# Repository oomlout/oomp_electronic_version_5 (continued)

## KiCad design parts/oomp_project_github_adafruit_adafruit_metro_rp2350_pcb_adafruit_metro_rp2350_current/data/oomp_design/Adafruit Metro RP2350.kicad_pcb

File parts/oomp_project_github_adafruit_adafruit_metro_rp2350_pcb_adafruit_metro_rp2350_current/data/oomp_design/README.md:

# OOMP KiCad design copy

Open `Adafruit Metro RP2350.kicad_pro` (or the `.kicad_pcb` / `.kicad_sch`) in KiCad. Local OOMP libraries are under `libraries/`. Original inputs are preserved in [../original/](../original/).

Only verified unchanged installed KiCad defaults were renamed. Modified, custom, unmatched and unavailable items remain unchanged. Soldering variants are never swapped during conversion. Existing pad coordinates, nets and UUIDs are preserved.

See [conversion_report.yaml](conversion_report.yaml) for every conversion and skip. Copy this directory before editing; regeneration refuses to overwrite edited design files.

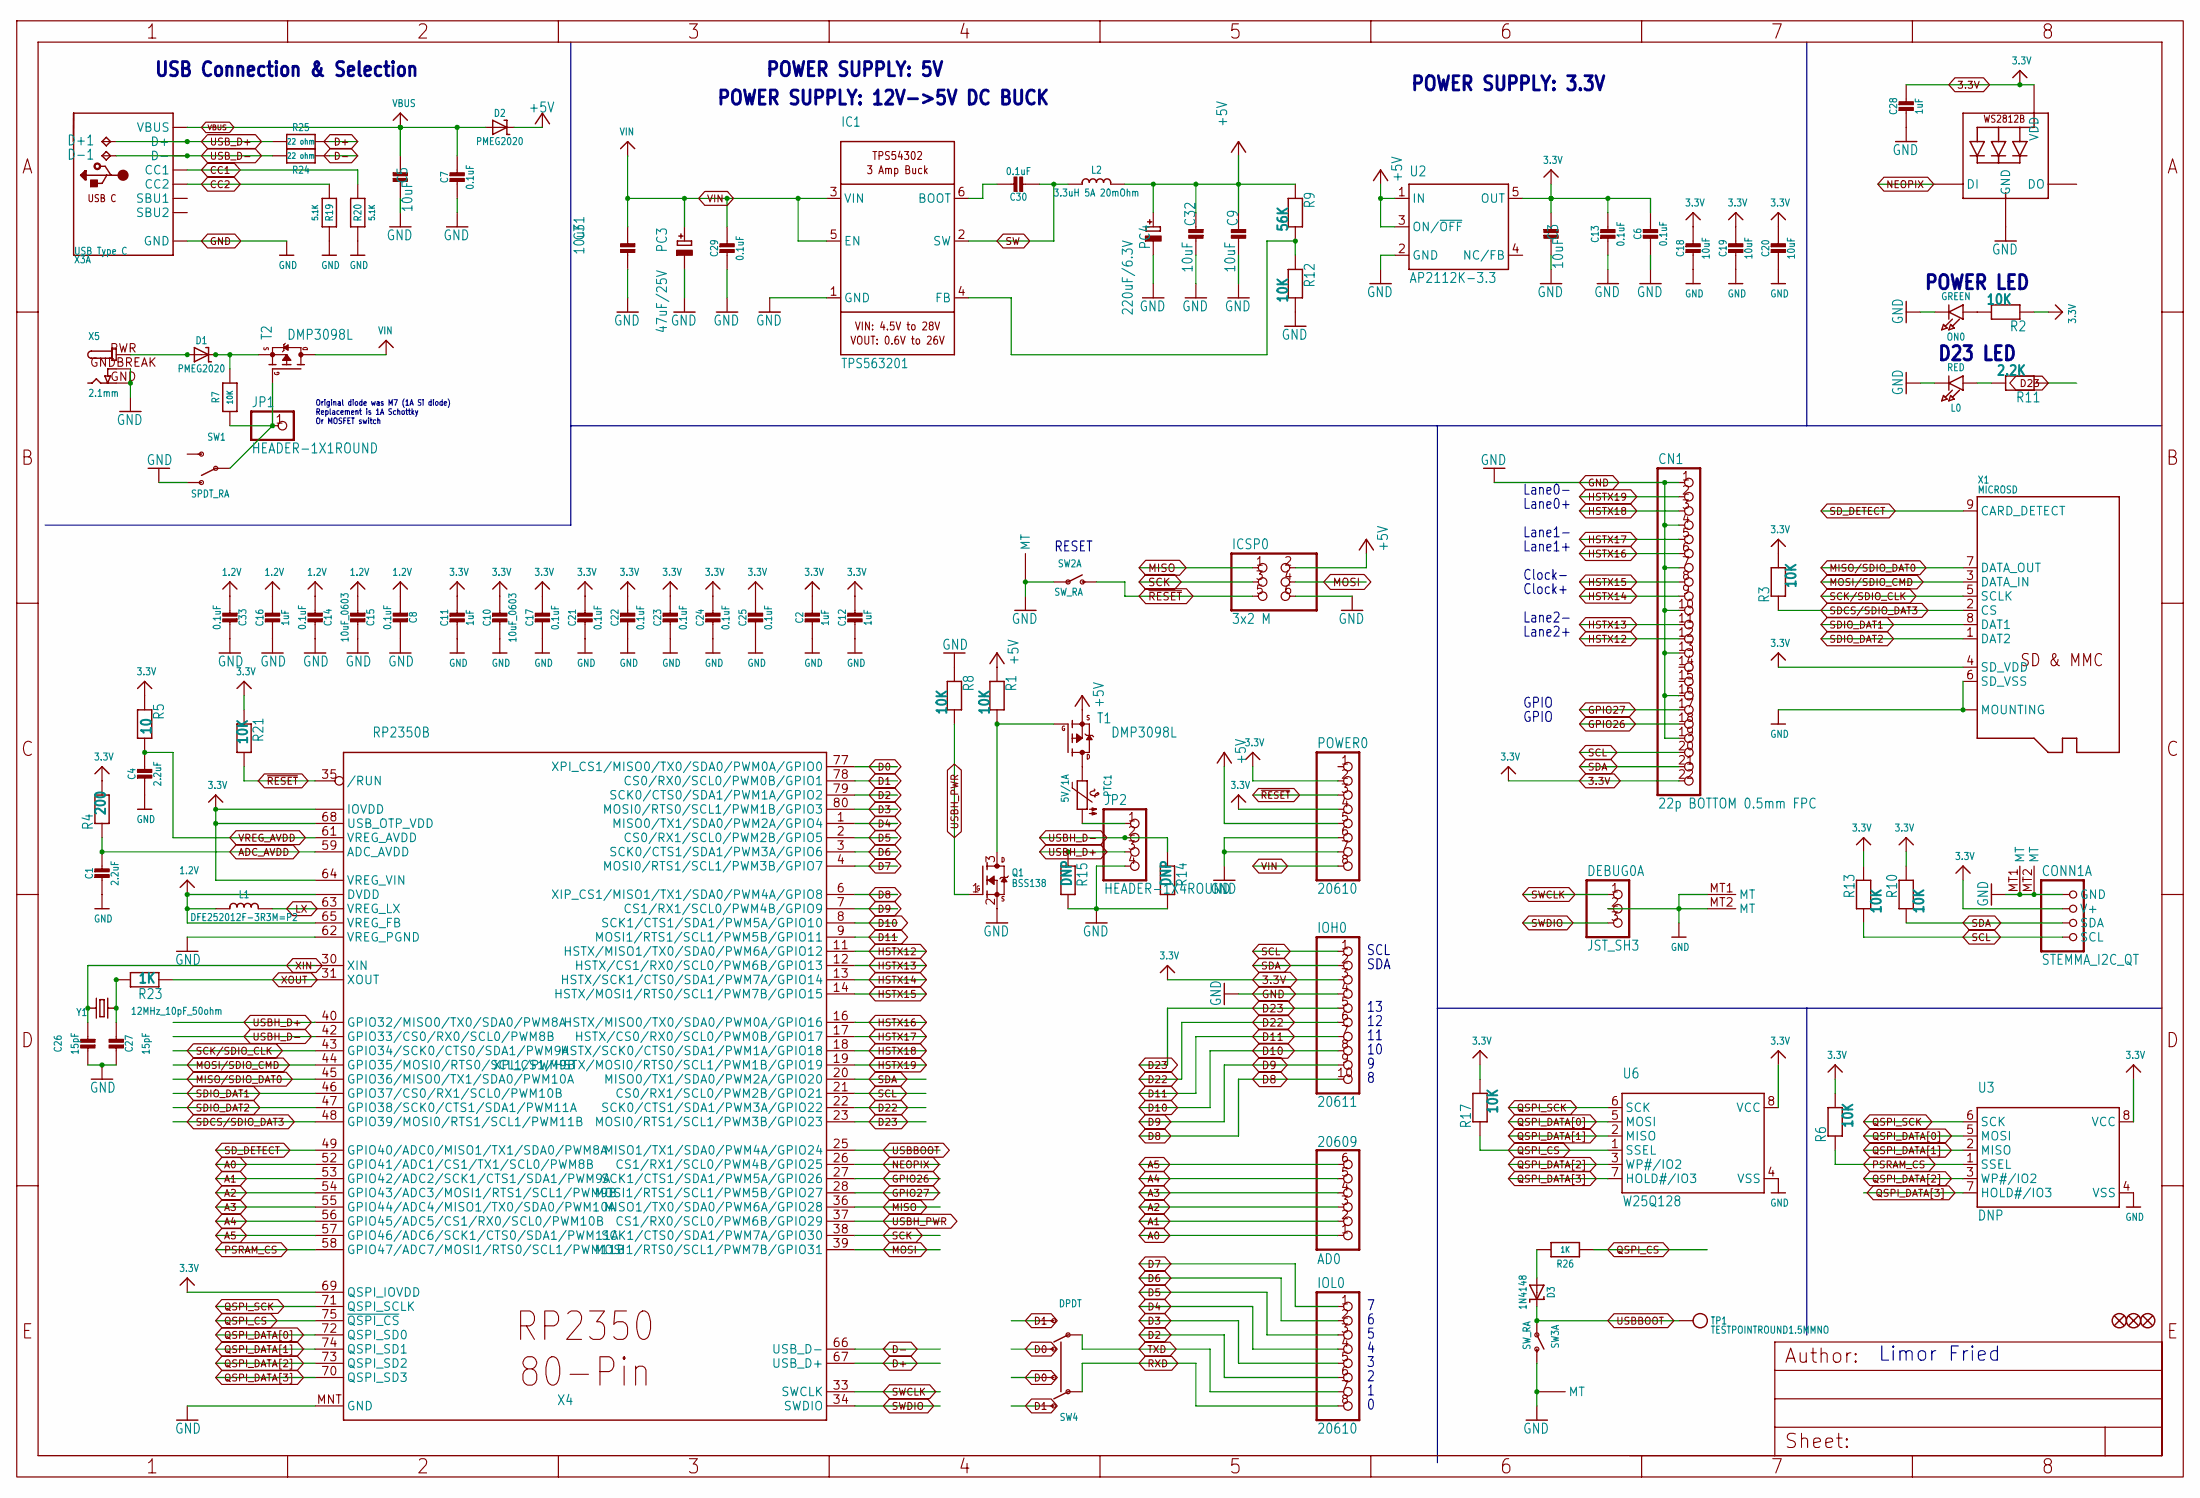
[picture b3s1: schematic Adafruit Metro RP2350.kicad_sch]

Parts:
AD0: 20609; 1X06_OVALWAVE
C1, C4: 2.2uF; 0603-NO
C2, C11, C12, C16, C28: 1uF; 0603-NO
C3, C5, C9, C18, C19, C20, C31, C32: 10uF; 0805-NO
C6, C7, C8, C13, C14, C17, C21, C22, C23, C24, C25, C29, C30, C33: 0.1uF; 0603-NO
C10, C15: 10uF_0603; 0603-NO_WIDE
C26, C27: 15pF; 0603-NO
CN1: 22p BOTTOM 0.5mm FPC; FPC_22PIN
CONN1: STEMMA_I2C_QT; JST_SH4; LCSC C2845363
D1, D2: PMEG2020; SOD-323
D3: 1N4148; SOD-323
D+1: TPB1,27; B1,27
D-1: TPB1,27; B1,27
DEBUG0: JST_SH3; JST_SH3_RA
FD1, FD2, FD3: FIDUCIAL_1MM
IC1: TPS563201; SOT23-6
ICSP0: 3x2 M; 2X03_ROUND_70MIL
IOH0: 20611; 1X10_OVALWAVE
IOL0: 20610; 1X08_OVALWAVE
JP1: HEADER-1X1ROUND; 1X01_ROUND
JP2: HEADER-1X4ROUND; 1X04_ROUND
L0: RED; CHIPLED_0603_NOOUTLINE
L1: DFE252012F-3R3M=P2; INDUCTOR_1007
L2: 3.3uH 5A 20mOhm; INDUCTOR_0603S
LED2: WS2812B_3535FULL; LED3535_FULLPADS
ON0: GREEN; CHIPLED_0603_NOOUTLINE
PC3: 47uF/25V; PANASONIC_D
PC4: 220uF/6.3V; PANASONIC_D
POWER0: 20610; 1X08_OVALWAVE
PTC1: 5V/1A; 0805-NO
Q1: BSS138; SOT23-WIDE
R1, R2, R3, R6, R7, R8, R10, R12, R13, R17, R21: 10K; 0603-NO
R4: 200; 0603-NO
R5: 10; 0603-NO
R9: 56K; 0603-NO
R11: 2.2K; 0603-NO
R14, R15: DNP; 0603-NO
R19, R20: 5.1K; 0603-NO
R23, R26: 1K; 0603-NO
R24, R25: 22 ohm; 0603-NO
SW1: SPDT_RA; SPDT_SMT_SSSS811101
SW2, SW3: SW_RA; SPST_TACTILE_RA; LCSC C778159
SW4: DPDT; EG1390; LCSC C2837066
T1, T2: DMP3098L; SOT23-WIDE
TP1: TESTPOINTROUND1.5MMNO; TESTPOINT_ROUND_1.5MM_NO
U2: AP2112K-3.3; SOT23-DBV
U3: DNP; SOIC8_208MIL
U6: W25Q128; SOIC8_208MIL
X1: MICROSD; MOLEX_104031-0811
X3: USB Type C; USB_C_CUSB31-CFM2AX-01-X; LCSC C165948
X4: RP2350B; QFN80
X5: 2.1mm; DCJACK_2MM_PTH
Y1: 12MHz_10pF_50ohm; CRYSTAL_2.5X2

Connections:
1.2V: C8.2, C14.2, C15.2, C16.1, C33.2, L1.P$1 (1), X4.10 (DVDD), X4.32 (DVDD), X4.51 (DVDD), X4.65 (VREG_FB)
3.3V: C2.1, C3.2, C6.2, C10.1, C11.1, C12.1, C13.1, C17.1, C18.1, C19.1, C20.1, C21.1, C22.1, C23.1, C24.1, C25.1, C28.1, CN1.22, CONN1.2 (V+), IOH0.3, LED2.2 (VDD), POWER0.2, POWER0.4, R2.1, R3.2, R4.2, R5.1, R6.2, R10.1, R13.1, R17.2, R21.1, U2.5 (OUT), U3.8 (VCC), U6.8 (VCC), X1.4 (SD_VDD), X4.5 (IOVDD), X4.15 (IOVDD), X4.24 (IOVDD), X4.29 (IOVDD), X4.41 (IOVDD), X4.50 (IOVDD), X4.60 (IOVDD), X4.64 (VREG_VIN), X4.68 (USB_OTP_VDD), X4.69 (QSPI_IOVDD), X4.76 (IOVDD)
+5V: C9.2, C32.2, D2.C, ICSP0.2, L2.P$2 (2), PC4.+, POWER0.5, R1.1, R9.1, T1.2 (S), U2.1 (IN), U2.3 (ON/~OFF)
A0: AD0.1, X4.52 (GPIO41/ADC1/CS1/TX1/SCL0/PWM8B)
A1: AD0.2, X4.53 (GPIO42/ADC2/SCK1/CTS1/SDA1/PWM9A)
A2: AD0.3, X4.54 (GPIO43/ADC3/MOSI1/RTS1/SCL1/PWM9B)
A3: AD0.4, X4.55 (GPIO44/ADC4/MISO1/TX0/SDA0/PWM10A)
A4: AD0.5, X4.56 (GPIO45/ADC5/CS1/RX0/SCL0/PWM10B)
A5: AD0.6, X4.57 (GPIO46/ADC6/SCK1/CTS0/SDA1/PWM11A)
ADC_AVDD: C1.1, R4.1, X4.59 (ADC_AVDD)
CC1: R20.2, X3.A5 (CC1)
CC2: R19.2, X3.B5 (CC2)
D0: SW4.O2, SW4.S1, X4.77 (XPI_CS1/MISO0/TX0/SDA0/PWM0A/GPIO0)
D1: SW4.O1, SW4.S2, X4.78 (CS0/RX0/SCL0/PWM0B/GPIO1)
D2: IOL0.6, X4.79 (SCK0/CTS0/SDA1/PWM1A/GPIO2)
D3: IOL0.5, X4.80 (MOSI0/RTS0/SCL1/PWM1B/GPIO3)
D4: IOL0.4, X4.1 (MISO0/TX1/SDA0/PWM2A/GPIO4)
D5: IOL0.3, X4.2 (CS0/RX1/SCL0/PWM2B/GPIO5)
D6: IOL0.2, X4.3 (SCK0/CTS1/SDA1/PWM3A/GPIO6)
D7: IOL0.1, X4.4 (MOSI0/RTS1/SCL1/PWM3B/GPIO7)
D8: IOH0.10, X4.6 (XIP_CS1/MISO1/TX1/SDA0/PWM4A/GPIO8)
D9: IOH0.9, X4.7 (CS1/RX1/SCL0/PWM4B/GPIO9)
D10: IOH0.8, X4.8 (SCK1/CTS1/SDA1/PWM5A/GPIO10)
D11: IOH0.7, X4.9 (MOSI1/RTS1/SCL1/PWM5B/GPIO11)
D22: IOH0.6, X4.22 (SCK0/CTS1/SDA1/PWM3A/GPIO22)
D23: IOH0.5, R11.1, X4.23 (MOSI0/RTS1/SCL1/PWM3B/GPIO23)
D+: R25.2, X4.67 (USB_D+)
D-: R24.2, X4.66 (USB_D-)
GND: C1.2, C2.2, C3.1, C4.2, C5.1, C6.1, C7.2, C8.1, C9.1, C10.2, C11.2, C12.2, C13.2, C14.1, C15.1, C16.2, C17.2, C18.2, C19.2, C20.2, C21.2, C22.2, C23.2, C24.2, C25.2, C26.1, C27.1, C28.2, C29.2, C31.1, C32.1, C33.1, CN1.1, CN1.4, CN1.7, CN1.10, CN1.13, CN1.16, CN1.19, CONN1.1 (GND), CONN1.MT1 (MT), CONN1.MT2 (MT), DEBUG0.2, DEBUG0.MT1 (MT), DEBUG0.MT2 (MT), IC1.1 (GND), ICSP0.6, IOH0.4, JP2.4, L0.C, LED2.4 (GND), ON0.C, PC3.-, PC4.-, POWER0.6, POWER0.7, Q1.2 (S), R8.1, R12.2, R14.1, R15.1, R19.1, R20.1, SW1.A (O), SW2.1, SW2.MT1 (MT), SW2.MT2 (MT), SW3.2 (S), SW3.MT1 (MT), SW3.MT2 (MT), U2.2 (GND), U3.4 (VSS), U6.4 (VSS), X1.6 (SD_VSS), X1.10 (MOUNTING), X1.G1 (MOUNTING), X1.G2 (MOUNTING), X1.G3 (MOUNTING), X1.G4 (MOUNTING), X3.A1B12 (GND), X3.B1A12 (GND), X4.62 (VREG_PGND), X4.MNT (GND), X5.GND, X5.GNDBREAK
GPIO26: CN1.18, X4.27 (SCK1/CTS1/SDA1/PWM5A/GPIO26)
GPIO27: CN1.17, X4.28 (MOSI1/RTS1/SCL1/PWM5B/GPIO27)
HSTX12: CN1.12, X4.11 (HSTX/MISO1/TX0/SDA0/PWM6A/GPIO12)
HSTX13: CN1.11, X4.12 (HSTX/CS1/RX0/SCL0/PWM6B/GPIO13)
HSTX14: CN1.9, X4.13 (HSTX/SCK1/CTS0/SDA1/PWM7A/GPIO14)
HSTX15: CN1.8, X4.14 (HSTX/MOSI1/RTS0/SCL1/PWM7B/GPIO15)
HSTX16: CN1.6, X4.16 (HSTX/MISO0/TX0/SDA0/PWM0A/GPIO16)
HSTX17: CN1.5, X4.17 (HSTX/CS0/RX0/SCL0/PWM0B/GPIO17)
HSTX18: CN1.3, X4.18 (HSTX/SCK0/CTS0/SDA1/PWM1A/GPIO18)
HSTX19: CN1.2, X4.19 (XPI_CS1/HSTX/MOSI0/RTS0/SCL1/PWM1B/GPIO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)
LX: L1.P$2 (2), X4.63 (VREG_LX)
MISO: ICSP0.1, X4.36 (MISO1/TX0/SDA0/PWM6A/GPIO28)
MISO/SDIO_DAT0: X1.7 (DATA_OUT), X4.45 (GPIO36/MISO0/TX1/SDA0/PWM10A)
MOSI: ICSP0.4, X4.39 (MOSI1/RTS0/SCL1/PWM7B/GPIO31)
MOSI/SDIO_CMD: X1.3 (DATA_IN), X4.44 (GPIO35/MOSI0/RTS0/SCL1/PWM9B)
unnamed: L0.A, R11.2
unnamed: ON0.A, R2.2
unnamed: JP2.1, PTC1.1
unnamed: PTC1.2, T1.3 (D)
unnamed: Q1.3 (D), R1.2, T1.1 (G)
unnamed: D3.A, R26.2
unnamed: C30.1, IC1.6 (BOOT)
unnamed: IC1.4 (FB), R9.2, R12.1
unnamed: C27.2, R23.1, Y1.3 (2)
unnamed: D1.C, R7.2, T2.2 (S)
NEOPIX: LED2.1 (DI), X4.26 (CS1/RX1/SCL0/PWM4B/GPIO25)
PSRAM_CS: R6.1, U3.1 (SSEL), X4.58 (GPIO47/ADC7/MOSI1/RTS0/SCL1/PWM11B)
PWRIN: D1.A, X5.PWR
PWR_SWITCH: JP1.1, R7.1, SW1.B, T2.1 (G)
QSPI_CS: R17.1, R26.1, U6.1 (SSEL), X4.75 (~QSPI_CS)
QSPI_DATA[0]: U3.5 (MOSI), U6.5 (MOSI), X4.72 (QSPI_SD0)
QSPI_DATA[1]: U3.2 (MISO), U6.2 (MISO), X4.74 (QSPI_SD1)
QSPI_DATA[2]: U3.3 (WP#/IO2), U6.3 (WP#/IO2), X4.73 (QSPI_SD2)
QSPI_DATA[3]: U3.7 (HOLD#/IO3), U6.7 (HOLD#/IO3), X4.70 (QSPI_SD3)
QSPI_SCK: U3.6 (SCK), U6.6 (SCK), X4.71 (QSPI_SCLK)
RXD: IOL0.8, SW4.P1
SCK: ICSP0.3, X4.38 (SCK1/CTS0/SDA1/PWM7A/GPIO30)
SCK/SDIO_CLK: X1.5 (SCLK), X4.43 (GPIO34/SCK0/CTS0/SDA1/PWM9A)
SCL: CN1.20, CONN1.4 (SCL), IOH0.1, R13.2, X4.21 (CS0/RX1/SCL0/PWM2B/GPIO21)
SDA: CN1.21, CONN1.3 (SDA), IOH0.2, R10.2, X4.20 (MISO0/TX1/SDA0/PWM2A/GPIO20)
SDCS/SDIO_DAT3: R3.1, X1.2 (CS), X4.48 (GPIO39/MOSI0/RTS1/SCL1/PWM11B)
SDIO_DAT1: X1.8 (DAT1), X4.46 (GPIO37/CS0/RX1/SCL0/PWM10B)
SDIO_DAT2: X1.1 (DAT2), X4.47 (GPIO38/SCK0/CTS1/SDA1/PWM11A)
SD_DETECT: X1.9 (CARD_DETECT), X4.49 (GPIO40/ADC0/MISO1/TX1/SDA0/PWM8A)
SW: C30.2, IC1.2 (SW), L2.P$1 (1)
SWCLK: DEBUG0.1, X4.33 (SWCLK)
SWDIO: DEBUG0.3, X4.34 (SWDIO)
TXD: IOL0.7, SW4.P2
USBBOOT: D3.C, SW3.1, TP1.P$1, X4.25 (MISO1/TX1/SDA0/PWM4A/GPIO24)
USBH_D+: JP2.3, R15.2, X4.40 (GPIO32/MISO0/TX0/SDA0/PWM8A)
USBH_D-: JP2.2, R14.2, X4.42 (GPIO33/CS0/RX0/SCL0/PWM8B)
USBH_PWR: Q1.1 (G), R8.2, X4.37 (CS1/RX0/SCL0/PWM6B/GPIO29)
USB_D+: D+1.TP, R25.1, X3.A6 (D+), X3.B6 (D+)
USB_D-: D-1.TP, R24.1, X3.A7 (D-), X3.B7 (D-)
VBUS: C5.2, C7.1, D2.A, X3.A4B9 (VBUS), X3.B4A9 (VBUS)
VIN: C29.1, C31.2, IC1.3 (VIN), IC1.5 (EN), PC3.+, POWER0.8, T2.3 (D)
VREG_AVDD: C4.1, R5.2, X4.61 (VREG_AVDD)
XIN: C26.2, X4.30 (XIN), Y1.1
XOUT: R23.2, X4.31 (XOUT)
~RESET: ICSP0.5, POWER0.3, R21.2, SW2.2 (S), X4.35 (/RUN)

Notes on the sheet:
SCL
Clock+
Lane0+
D23 LED
POWER SUPPLY: 12V->5V DC BUCK
Lane1-
Lane2+
POWER LED
GPIO
USB Connection & Selection
POWER SUPPLY: 5V
Limor Fried
Clock-
Original diode was M7 (1A Si diode) Replacement is 1A Schottky Or MOSFET switch
POWER SUPPLY: 3.3V
Lane2-
RESET
Lane0-
SDA
Lane1+

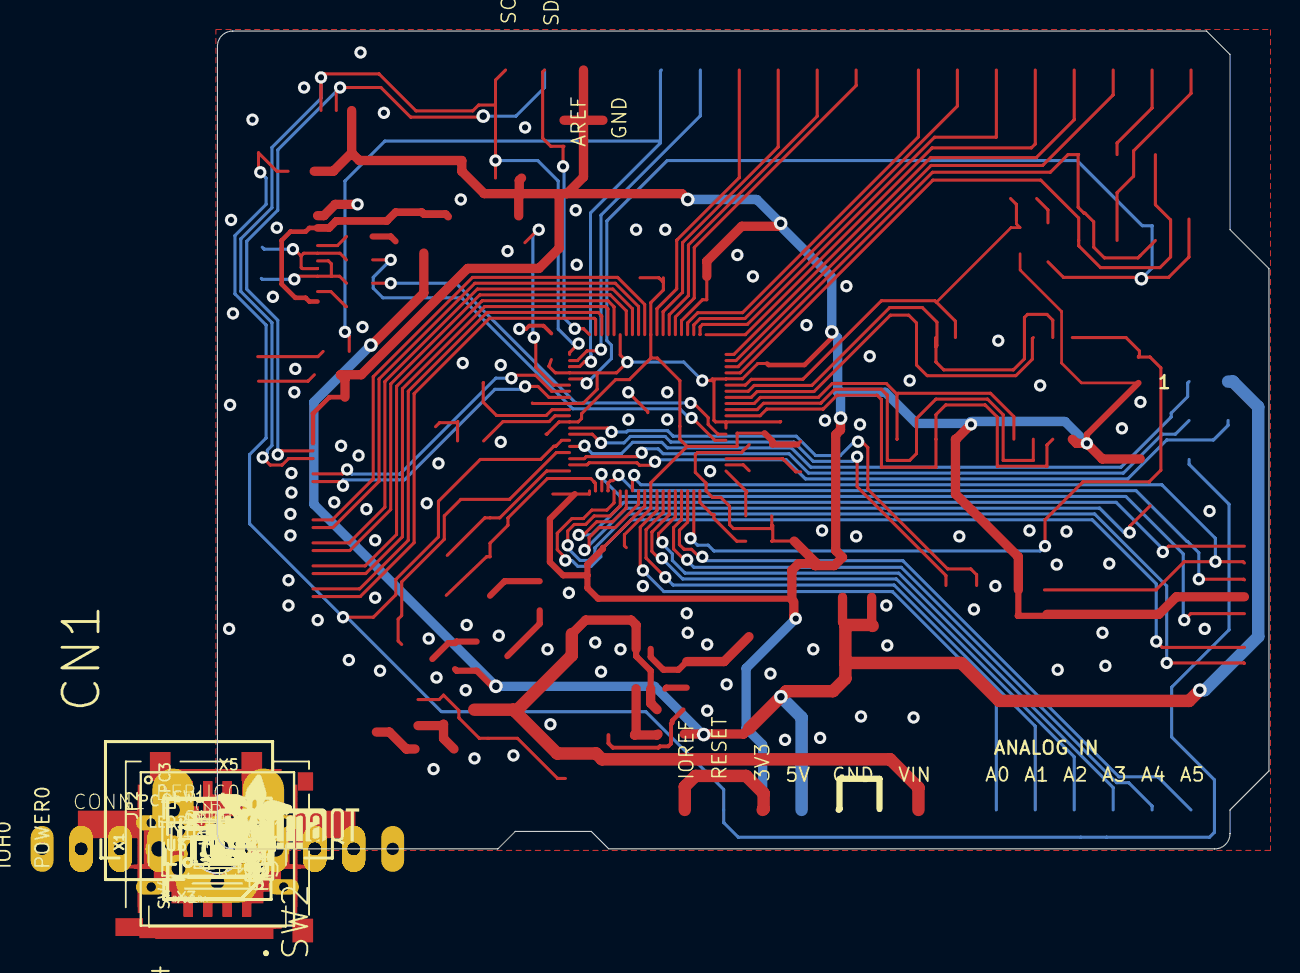
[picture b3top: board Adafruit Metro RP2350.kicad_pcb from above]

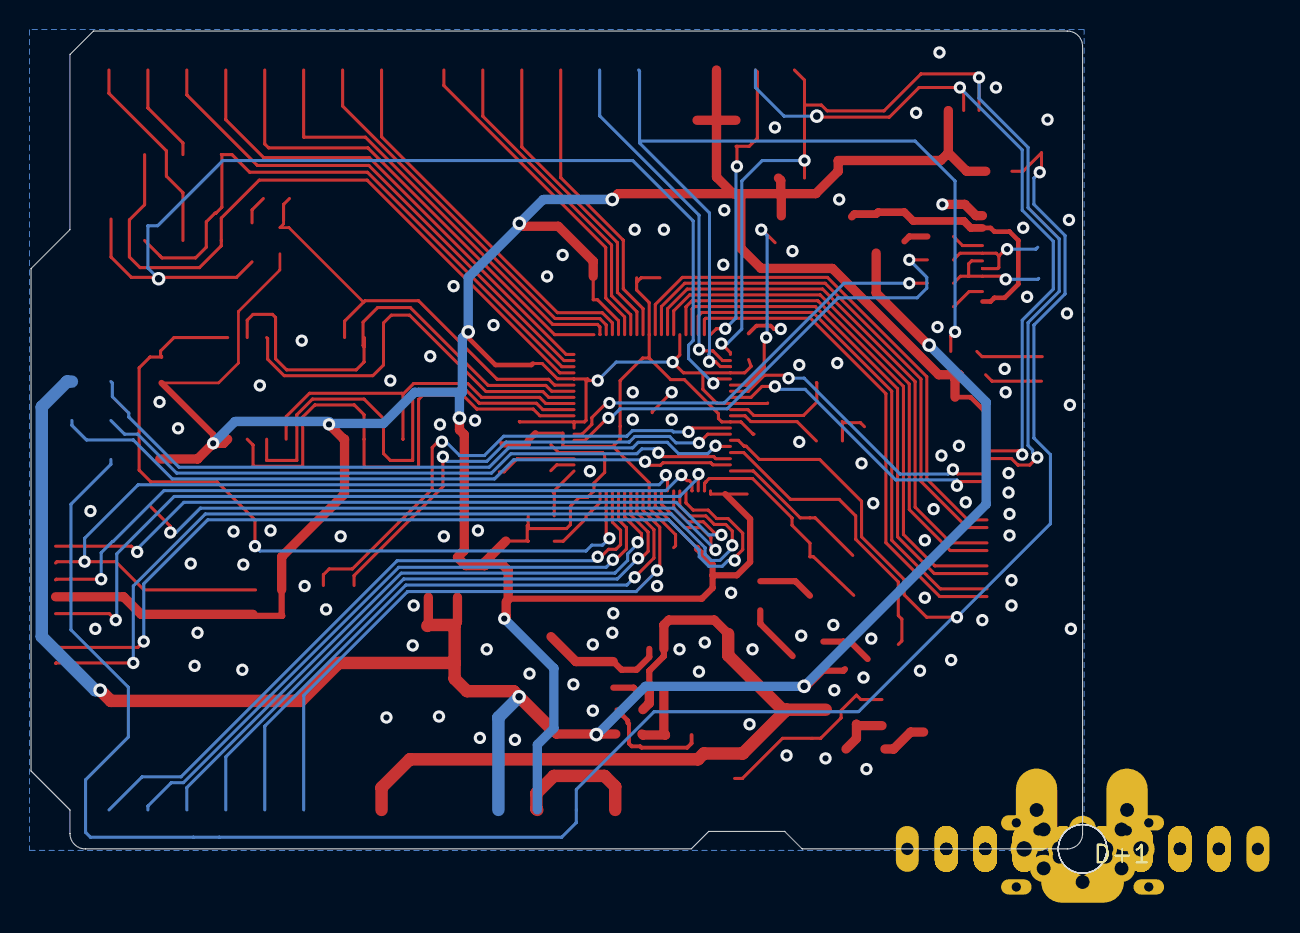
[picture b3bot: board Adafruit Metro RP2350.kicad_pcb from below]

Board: 2 copper layers, 68.6 x 53.3 mm, 174 parts (5 on the bottom side), 89 nets.

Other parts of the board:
PLABEL0: PLABEL0
PLABEL1: PLABEL1
PLABEL2: PLABEL2
PLABEL3: PLABEL3
PLABEL4: PLABEL4
PLABEL5: PLABEL5
PLABEL6: PLABEL6
PLABEL7: PLABEL7
PLABEL8: PLABEL8
PLABEL10: PLABEL10
PLABEL11: PLABEL11
PLABEL12: PLABEL12
PLABEL13: PLABEL13
PLABEL14: PLABEL14
PLABEL15: PLABEL15
PLABEL16: PLABEL16
PLABEL17: PLABEL17
PLABEL18: PLABEL18
PLABEL19: PLABEL19
PLABEL20: PLABEL20
PLABEL21: PLABEL21
PLABEL22: PLABEL22
PLABEL23: PLABEL23
PLABEL24: PLABEL24
PLABEL25: PLABEL25
PLABEL26: PLABEL26
PLABEL27: PLABEL27
PLABEL28: PLABEL28
PLABEL29: PLABEL29
PLABEL30: PLABEL30
PLABEL31: PLABEL31
PLABEL32: PLABEL32
PLABEL33: PLABEL33
PLABEL34: PLABEL34
PLABEL35: PLABEL35
PLABEL36: PLABEL36
PLABEL37: PLABEL37
PLABEL38: PLABEL38
PLABEL39: PLABEL39
PLABEL40: PLABEL40
PLABEL41: PLABEL41
PLABEL42: PLABEL42
PLABEL43: PLABEL43
PLABEL46: PLABEL46
PLABEL47: PLABEL47
PLABEL48: PLABEL48
PLABEL49: PLABEL49
PLABEL50: PLABEL50
PLABEL51: PLABEL51
PLABEL52: PLABEL52
PLABEL53: PLABEL53
PLABEL54: PLABEL54
PLABEL55: PLABEL55
PLABEL56: PLABEL56
PLABEL57: PLABEL57
PLABEL59: PLABEL59
PLABEL60: PLABEL60
PLABEL62: PLABEL62
PLABEL63: PLABEL63
PLABEL64: PLABEL64
PLABEL65: PLABEL65
PLABEL66: PLABEL66
PLABEL67: PLABEL67
PLABEL68: PLABEL68
PLABEL69: PLABEL69
PLABEL70: PLABEL70
U$3: STEMMAQT
U$11: PCBFEAT-REV-040
U$47: METRO_RP2350_TOP
U$50: ADAFRUIT_5MM
U$71: METRO_RP2350_BOT
UNK_HOLE_0: dummyfp0
UNK_HOLE_1: dummyfp1
UNK_HOLE_2: dummyfp2
UNK_HOLE_3: dummyfp3

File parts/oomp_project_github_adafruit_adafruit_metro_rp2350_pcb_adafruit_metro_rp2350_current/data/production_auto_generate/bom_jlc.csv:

Comment,Designator,Footprint,LCSC Part #
,JP1,Adafruit Metro RP2350-import-fps:1X01_ROUND,C7501259
,JP2,Adafruit Metro RP2350-import-fps:1X04_ROUND,C42431795
,U$50,Adafruit Metro RP2350-import-fps:ADAFRUIT_5MM,
,U$71,Adafruit Metro RP2350-import-fps:METRO_RP2350_BOT,
,U$47,Adafruit Metro RP2350-import-fps:METRO_RP2350_TOP,
,U$11,Adafruit Metro RP2350-import-fps:PCBFEAT-REV-040,
,PLABEL0,Adafruit Metro RP2350-import-fps:PLABEL0,
,PLABEL1,Adafruit Metro RP2350-import-fps:PLABEL1,
,PLABEL10,Adafruit Metro RP2350-import-fps:PLABEL10,
,PLABEL11,Adafruit Metro RP2350-import-fps:PLABEL11,
,PLABEL12,Adafruit Metro RP2350-import-fps:PLABEL12,
,PLABEL13,Adafruit Metro RP2350-import-fps:PLABEL13,
,PLABEL14,Adafruit Metro RP2350-import-fps:PLABEL14,
,PLABEL15,Adafruit Metro RP2350-import-fps:PLABEL15,
,PLABEL16,Adafruit Metro RP2350-import-fps:PLABEL16,
,PLABEL17,Adafruit Metro RP2350-import-fps:PLABEL17,
,PLABEL18,Adafruit Metro RP2350-import-fps:PLABEL18,
,PLABEL19,Adafruit Metro RP2350-import-fps:PLABEL19,
,PLABEL2,Adafruit Metro RP2350-import-fps:PLABEL2,
,PLABEL20,Adafruit Metro RP2350-import-fps:PLABEL20,
,PLABEL21,Adafruit Metro RP2350-import-fps:PLABEL21,
,PLABEL22,Adafruit Metro RP2350-import-fps:PLABEL22,
,PLABEL23,Adafruit Metro RP2350-import-fps:PLABEL23,
,PLABEL24,Adafruit Metro RP2350-import-fps:PLABEL24,
,PLABEL25,Adafruit Metro RP2350-import-fps:PLABEL25,
,PLABEL26,Adafruit Metro RP2350-import-fps:PLABEL26,
,PLABEL27,Adafruit Metro RP2350-import-fps:PLABEL27,
,PLABEL28,Adafruit Metro RP2350-import-fps:PLABEL28,
,PLABEL29,Adafruit Metro RP2350-import-fps:PLABEL29,
,PLABEL3,Adafruit Metro RP2350-import-fps:PLABEL3,
,PLABEL30,Adafruit Metro RP2350-import-fps:PLABEL30,
,PLABEL31,Adafruit Metro RP2350-import-fps:PLABEL31,
,PLABEL32,Adafruit Metro RP2350-import-fps:PLABEL32,
,PLABEL33,Adafruit Metro RP2350-import-fps:PLABEL33,
,PLABEL34,Adafruit Metro RP2350-import-fps:PLABEL34,
,PLABEL35,Adafruit Metro RP2350-import-fps:PLABEL35,
,PLABEL36,Adafruit Metro RP2350-import-fps:PLABEL36,
,PLABEL37,Adafruit Metro RP2350-import-fps:PLABEL37,
,PLABEL38,Adafruit Metro RP2350-import-fps:PLABEL38,
,PLABEL39,Adafruit Metro RP2350-import-fps:PLABEL39,
,PLABEL4,Adafruit Metro RP2350-import-fps:PLABEL4,
,PLABEL40,Adafruit Metro RP2350-import-fps:PLABEL40,
,PLABEL41,Adafruit Metro RP2350-import-fps:PLABEL41,
,PLABEL42,Adafruit Metro RP2350-import-fps:PLABEL42,
,PLABEL43,Adafruit Metro RP2350-import-fps:PLABEL43,
,PLABEL46,Adafruit Metro RP2350-import-fps:PLABEL46,
,PLABEL47,Adafruit Metro RP2350-import-fps:PLABEL47,
,PLABEL48,Adafruit Metro RP2350-import-fps:PLABEL48,
,PLABEL49,Adafruit Metro RP2350-import-fps:PLABEL49,
,PLABEL5,Adafruit Metro RP2350-import-fps:PLABEL5,
,PLABEL50,Adafruit Metro RP2350-import-fps:PLABEL50,
,PLABEL51,Adafruit Metro RP2350-import-fps:PLABEL51,
,PLABEL52,Adafruit Metro RP2350-import-fps:PLABEL52,
,PLABEL53,Adafruit Metro RP2350-import-fps:PLABEL53,
,PLABEL54,Adafruit Metro RP2350-import-fps:PLABEL54,
,PLABEL55,Adafruit Metro RP2350-import-fps:PLABEL55,
,PLABEL56,Adafruit Metro RP2350-import-fps:PLABEL56,
,PLABEL57,Adafruit Metro RP2350-import-fps:PLABEL57,
,PLABEL59,Adafruit Metro RP2350-import-fps:PLABEL59,
,PLABEL6,Adafruit Metro RP2350-import-fps:PLABEL6,
,PLABEL60,Adafruit Metro RP2350-import-fps:PLABEL60,
,PLABEL62,Adafruit Metro RP2350-import-fps:PLABEL62,
,PLABEL63,Adafruit Metro RP2350-import-fps:PLABEL63,
,PLABEL64,Adafruit Metro RP2350-import-fps:PLABEL64,
,PLABEL65,Adafruit Metro RP2350-import-fps:PLABEL65,
,PLABEL66,Adafruit Metro RP2350-import-fps:PLABEL66,
,PLABEL67,Adafruit Metro RP2350-import-fps:PLABEL67,
,PLABEL68,Adafruit Metro RP2350-import-fps:PLABEL68,
,PLABEL69,Adafruit Metro RP2350-import-fps:PLABEL69,
,PLABEL7,Adafruit Metro RP2350-import-fps:PLABEL7,
,PLABEL70,Adafruit Metro RP2350-import-fps:PLABEL70,
,PLABEL8,Adafruit Metro RP2350-import-fps:PLABEL8,
,U$3,Adafruit Metro RP2350-import-fps:STEMMAQT,
,TP1,Adafruit Metro RP2350-import-fps:TESTPOINT_ROUND_1.5MM_NO,
0.1uF,"C6,C7,C8,C13,C14,C17,C21,C22,C23,C24,C25,C29,C30,C33",Adafruit Metro RP2350-import-fps:0603-NO,C14663
10,R5,Adafruit Metro RP2350-import-fps:0603-NO,C22859
10K,"R1,R2,R3,R6,R7,R8,R10,R12,R13,R17,R21",Adafruit Metro RP2350-import-fps:0603-NO,C98220
10uF,"C3,C5,C9,C18,C19,C20,C31,C32",Adafruit Metro RP2350-import-fps:0805-NO,
10uF_0603,"C10,C15",Adafruit Metro RP2350-import-fps:0603-NO_WIDE,C19702
12MHz_10pF_50ohm,Y1,Adafruit Metro RP2350-import-fps:CRYSTAL_2.5X2,
15pF,"C26,C27",Adafruit Metro RP2350-import-fps:0603-NO,
1K,"R23,R26",Adafruit Metro RP2350-import-fps:0603-NO,C2907002
1N4148,D3,Adafruit Metro RP2350-import-fps:SOD-323,
1uF,"C2,C11,C12,C16,C28",Adafruit Metro RP2350-import-fps:0603-NO,C5673
2.1mm,X5,Adafruit Metro RP2350-import-fps:DCJACK_2MM_PTH,
2.2K,R11,Adafruit Metro RP2350-import-fps:0603-NO,C4190
2.2uF,"C1,C4",Adafruit Metro RP2350-import-fps:0603-NO,C23630
200,R4,Adafruit Metro RP2350-import-fps:0603-NO,C114664
20609,AD0,Adafruit Metro RP2350-import-fps:1X06_OVALWAVE,C37208
20610,"IOL0,POWER0",Adafruit Metro RP2350-import-fps:1X08_OVALWAVE,C492421
20611,IOH0,Adafruit Metro RP2350-import-fps:1X10_OVALWAVE,C57369
22 ohm,"R24,R25",Adafruit Metro RP2350-import-fps:0603-NO,C23345
220uF/6.3V,PC4,Adafruit Metro RP2350-import-fps:PANASONIC_D,
22p BOTTOM 0.5mm FPC,CN1,Adafruit Metro RP2350-import-fps:FPC_22PIN,
3.3uH 5A 20mOhm,L2,Adafruit Metro RP2350-import-fps:INDUCTOR_0603S,
3x2 M,ICSP0,Adafruit Metro RP2350-import-fps:2X03_ROUND_70MIL,
47uF/25V,PC3,Adafruit Metro RP2350-import-fps:PANASONIC_D,
5.1K,"R19,R20",Adafruit Metro RP2350-import-fps:0603-NO,C23186
56K,R9,Adafruit Metro RP2350-import-fps:0603-NO,C23206
5V/1A,PTC1,Adafruit Metro RP2350-import-fps:0805-NO,
AP2112K-3.3,U2,Adafruit Metro RP2350-import-fps:SOT23-DBV,
BSS138,Q1,Adafruit Metro RP2350-import-fps:SOT23-WIDE,C52895
DFE252012F-3R3M=P2,L1,Adafruit Metro RP2350-import-fps:INDUCTOR_1007,
DMP3098L,"T1,T2",Adafruit Metro RP2350-import-fps:SOT23-WIDE,
DNP,"R14,R15",Adafruit Metro RP2350-import-fps:0603-NO,
DNP,U3,Adafruit Metro RP2350-import-fps:SOIC8_208MIL,
DPDT,SW4,Adafruit Metro RP2350-import-fps:EG1390,
FIDUCIAL_1MM,"FD1,FD2,FD3",Adafruit Metro RP2350-import-fps:FIDUCIAL_1MM,
GREEN,ON0,Adafruit Metro RP2350-import-fps:CHIPLED_0603_NOOUTLINE,
JST_SH3,DEBUG0,Adafruit Metro RP2350-import-fps:JST_SH3_RA,
MICROSD,X1,Adafruit Metro RP2350-import-fps:MOLEX_104031-0811,
PMEG2020,"D1,D2",Adafruit Metro RP2350-import-fps:SOD-323,
RED,L0,Adafruit Metro RP2350-import-fps:CHIPLED_0603_NOOUTLINE,
RP2350B,X4,Adafruit Metro RP2350-import-fps:QFN80,
SPDT_RA,SW1,Adafruit Metro RP2350-import-fps:SPDT_SMT_SSSS811101,
STEMMA_I2C_QT,CONN1,Adafruit Metro RP2350-import-fps:JST_SH4,C160404
SW_RA,"SW2,SW3",Adafruit Metro RP2350-import-fps:SPST_TACTILE_RA,
"TPB1,27","D+1,D-1","Adafruit Metro RP2350-import-fps:B1,27",
TPS563201,IC1,Adafruit Metro RP2350-import-fps:SOT23-6,
USB Type C,X3,Adafruit Metro RP2350-import-fps:USB_C_CUSB31-CFM2AX-01-X,
W25Q128,U6,Adafruit Metro RP2350-import-fps:SOIC8_208MIL,
WS2812B_3535FULL,LED2,Adafruit Metro RP2350-import-fps:LED3535_FULLPADS,

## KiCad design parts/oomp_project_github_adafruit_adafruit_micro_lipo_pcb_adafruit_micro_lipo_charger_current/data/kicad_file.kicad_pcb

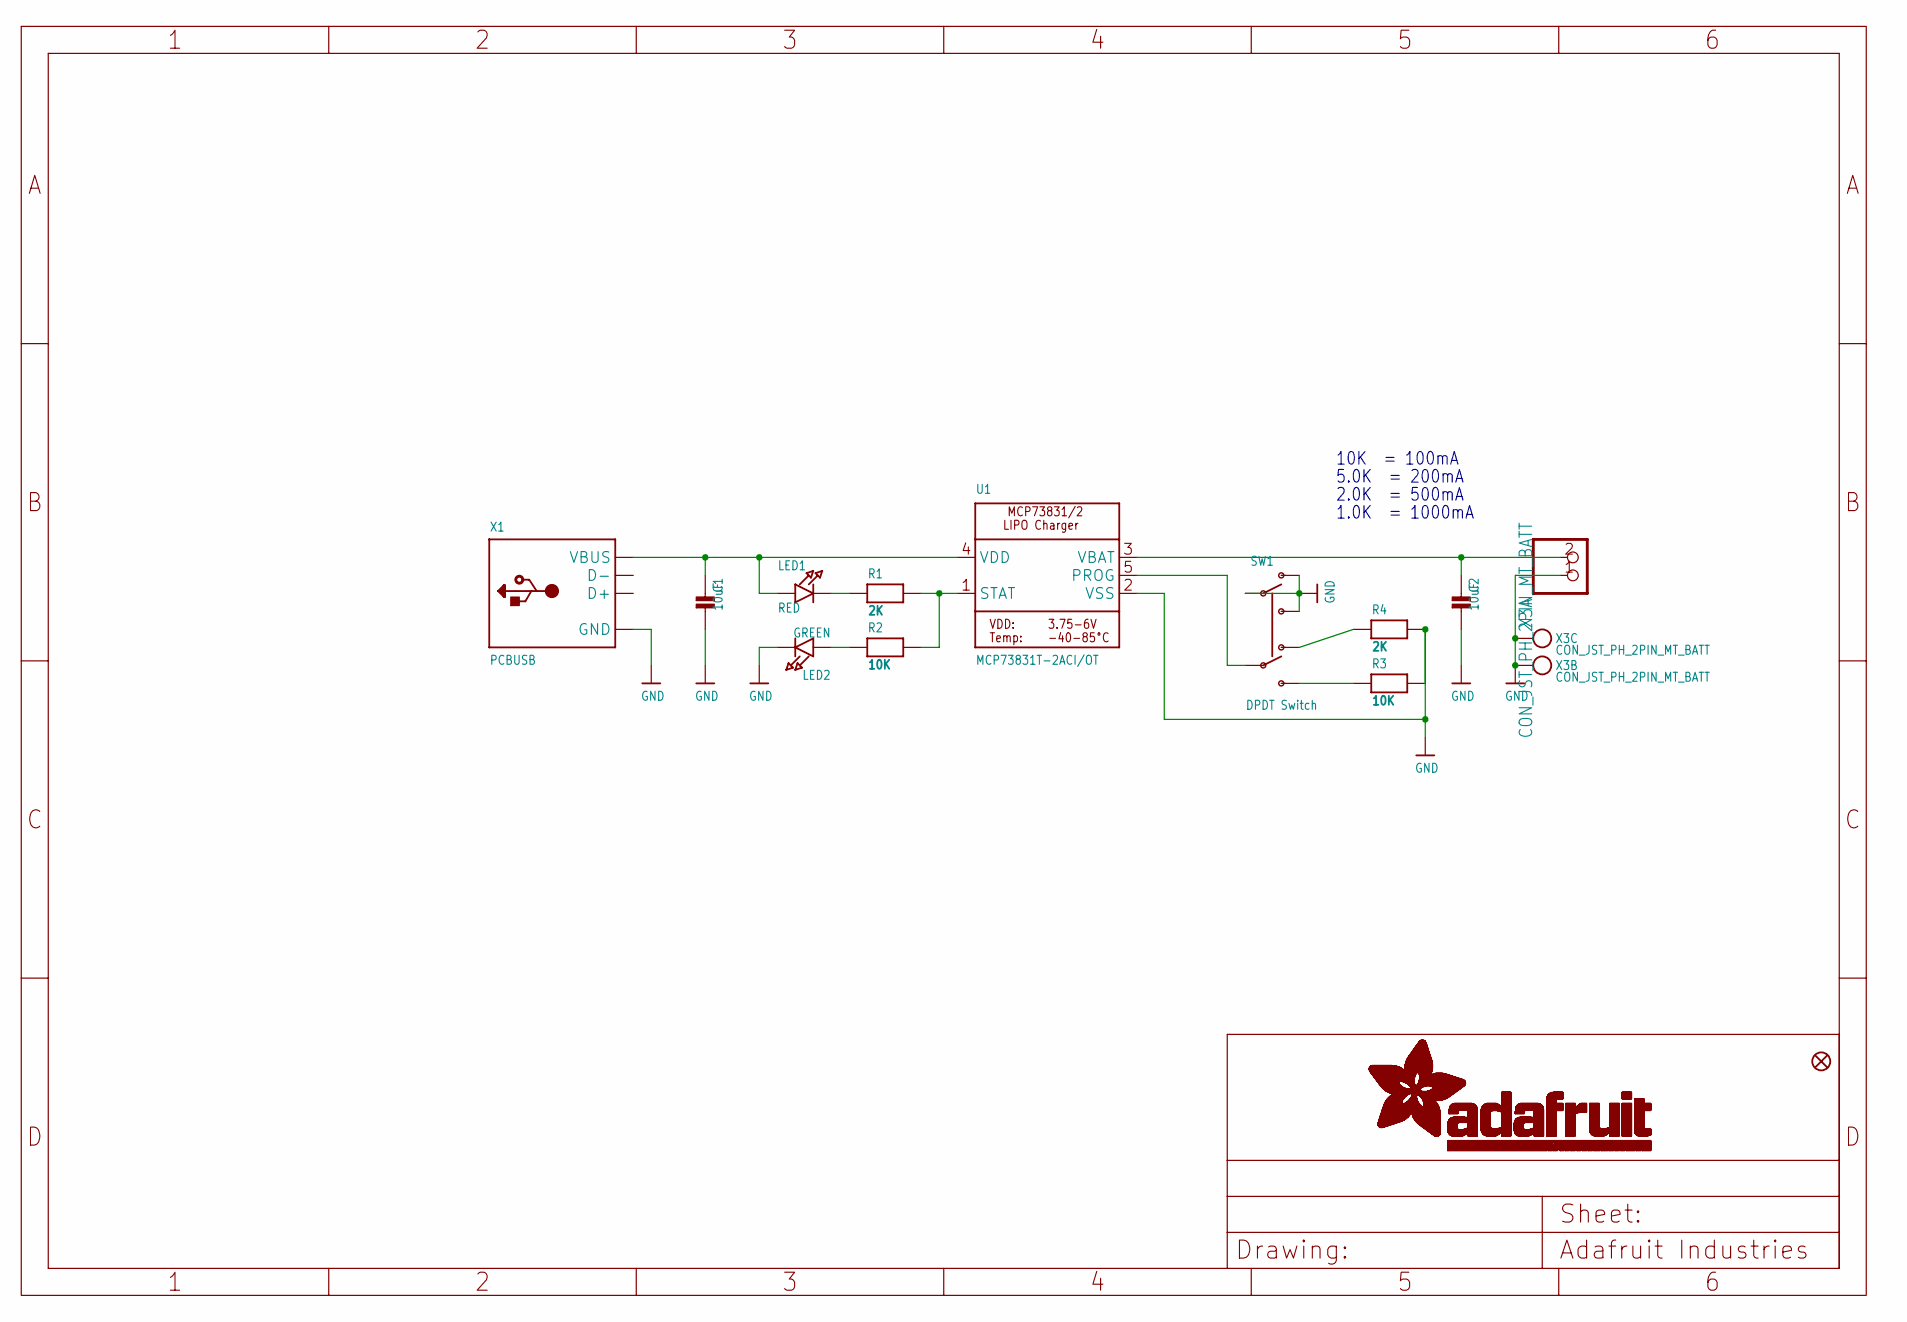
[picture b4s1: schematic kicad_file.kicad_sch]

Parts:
C1, C2: 10uF; 0805-NO
FID1: FIDUCIAL_1MM
LED1: RED; CHIPLED_0603_NOOUTLINE; JLC_ROTATION 270
LED2: GREEN; CHIPLED_0603_NOOUTLINE; JLC_ROTATION 270
R1, R4: 2K; 0603-NO
R2, R3: 10K; 0603-NO
SW1: DPDT Switch; EG1390; LCSC C2837066
U1: MCP73831T-2ACI/OT; SOT23-5; JLC_ROTATION 270
X1: PCBUSB; USBA_PCB
X3: CON_JST_PH_2PIN_MT_BATT; JSTPH2_BATT; LCSC C47647

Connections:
GND: C1.2, C2.2, LED2.C, R3.2, R4.2, SW1.O1, SW1.P1, SW1.S1, U1.2 (VSS), X1.GND, X3.1, X3.NC1, X3.NC2
unnamed: LED1.C, R1.1
unnamed: R1.2, R2.2, U1.1 (STAT)
unnamed: R3.1, SW1.S2
unnamed: R4.1, SW1.O2
unnamed: SW1.P2, U1.5 (PROG)
unnamed: LED2.A, R2.1
VBAT: C2.1, U1.3 (VBAT), X3.2
VDD: C1.1, LED1.A, U1.4 (VDD), X1.VCC (VBUS)

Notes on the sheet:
1.0K = 1000mA
5.0K = 200mA
10K = 100mA
2.0K = 500mA

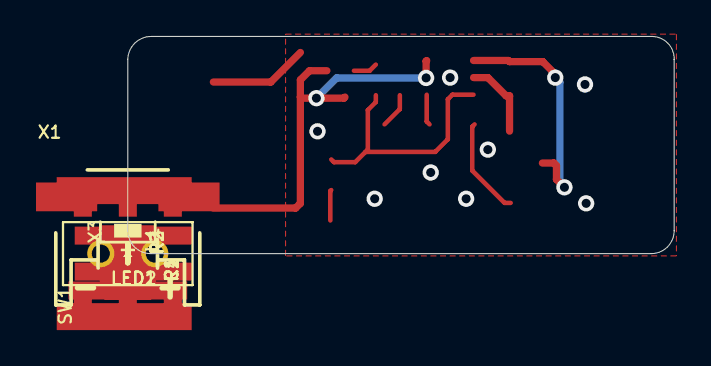
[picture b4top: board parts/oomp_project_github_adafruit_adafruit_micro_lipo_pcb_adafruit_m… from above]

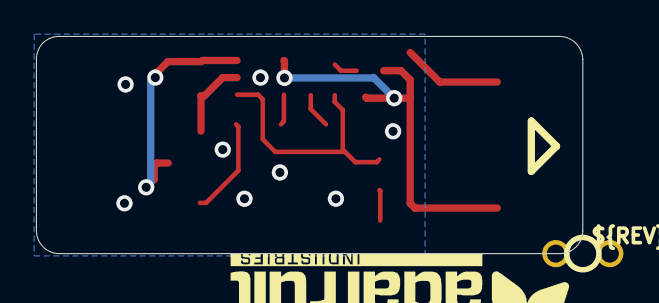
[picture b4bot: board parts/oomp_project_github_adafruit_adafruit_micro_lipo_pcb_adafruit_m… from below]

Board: 2 copper layers, 30.4 x 12.1 mm, 27 parts (5 on the bottom side), 9 nets.

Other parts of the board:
PLABEL0: PLABEL0
PLABEL1: PLABEL1
PLABEL2: PLABEL2
PLABEL3: PLABEL3
PLABEL4: PLABEL4
PLABEL5: PLABEL5
PLABEL6: PLABEL6
PLABEL7: PLABEL7
PLABEL8: PLABEL8
PLABEL9: PLABEL9
PLABEL10: PLABEL10
PLABEL11: PLABEL11
U$8: ADAFRUIT_TEXT_20MM
U$9: PCBFEAT-REV-040

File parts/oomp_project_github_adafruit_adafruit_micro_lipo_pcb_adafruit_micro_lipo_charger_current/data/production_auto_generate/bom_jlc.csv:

Comment,Designator,Footprint,LCSC Part #
,U$8,Adafruit MicroLipo Charger v2-import-fps:ADAFRUIT_TEXT_20MM,
,U$9,Adafruit MicroLipo Charger v2-import-fps:PCBFEAT-REV-040,
,PLABEL0,Adafruit MicroLipo Charger v2-import-fps:PLABEL0,
,PLABEL1,Adafruit MicroLipo Charger v2-import-fps:PLABEL1,
,PLABEL10,Adafruit MicroLipo Charger v2-import-fps:PLABEL10,
,PLABEL11,Adafruit MicroLipo Charger v2-import-fps:PLABEL11,
,PLABEL2,Adafruit MicroLipo Charger v2-import-fps:PLABEL2,
,PLABEL3,Adafruit MicroLipo Charger v2-import-fps:PLABEL3,
,PLABEL4,Adafruit MicroLipo Charger v2-import-fps:PLABEL4,
,PLABEL5,Adafruit MicroLipo Charger v2-import-fps:PLABEL5,
,PLABEL6,Adafruit MicroLipo Charger v2-import-fps:PLABEL6,
,PLABEL7,Adafruit MicroLipo Charger v2-import-fps:PLABEL7,
,PLABEL8,Adafruit MicroLipo Charger v2-import-fps:PLABEL8,
,PLABEL9,Adafruit MicroLipo Charger v2-import-fps:PLABEL9,
10K,"R2,R3",Adafruit MicroLipo Charger v2-import-fps:0603-NO,C98220
10uF,"C1,C2",Adafruit MicroLipo Charger v2-import-fps:0805-NO,
2K,"R1,R4",Adafruit MicroLipo Charger v2-import-fps:0603-NO,C22975
CON_JST_PH_2PIN_MT_BATT,X3,Adafruit MicroLipo Charger v2-import-fps:JSTPH2_BATT,
DPDT Switch,SW1,Adafruit MicroLipo Charger v2-import-fps:EG1390,
GREEN,LED2,Adafruit MicroLipo Charger v2-import-fps:CHIPLED_0603_NOOUTLINE,
MCP73831T-2ACI/OT,U1,Adafruit MicroLipo Charger v2-import-fps:SOT23-5,
PCBUSB,X1,Adafruit MicroLipo Charger v2-import-fps:USBA_PCB,
RED,LED1,Adafruit MicroLipo Charger v2-import-fps:CHIPLED_0603_NOOUTLINE,
